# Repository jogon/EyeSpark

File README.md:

EyeSpark
========
EyeSpark brings to users a new and innovative way of interacting with computers. It allows users to control their mouse and keyboard with only their eyes and head. EyeSpark consists of a head mounted device and an application running on the users computer. The head mounted device tracks eye and head movements and sends the information to the user's PC via USB. The EyeSpark application captures this information and uses it to create the mapping of eye and head gestures to mouse and keystrokes. Users can fully customize the mappings and tie them to specific applications, allowing EyeSpark to work with a variety of applications.

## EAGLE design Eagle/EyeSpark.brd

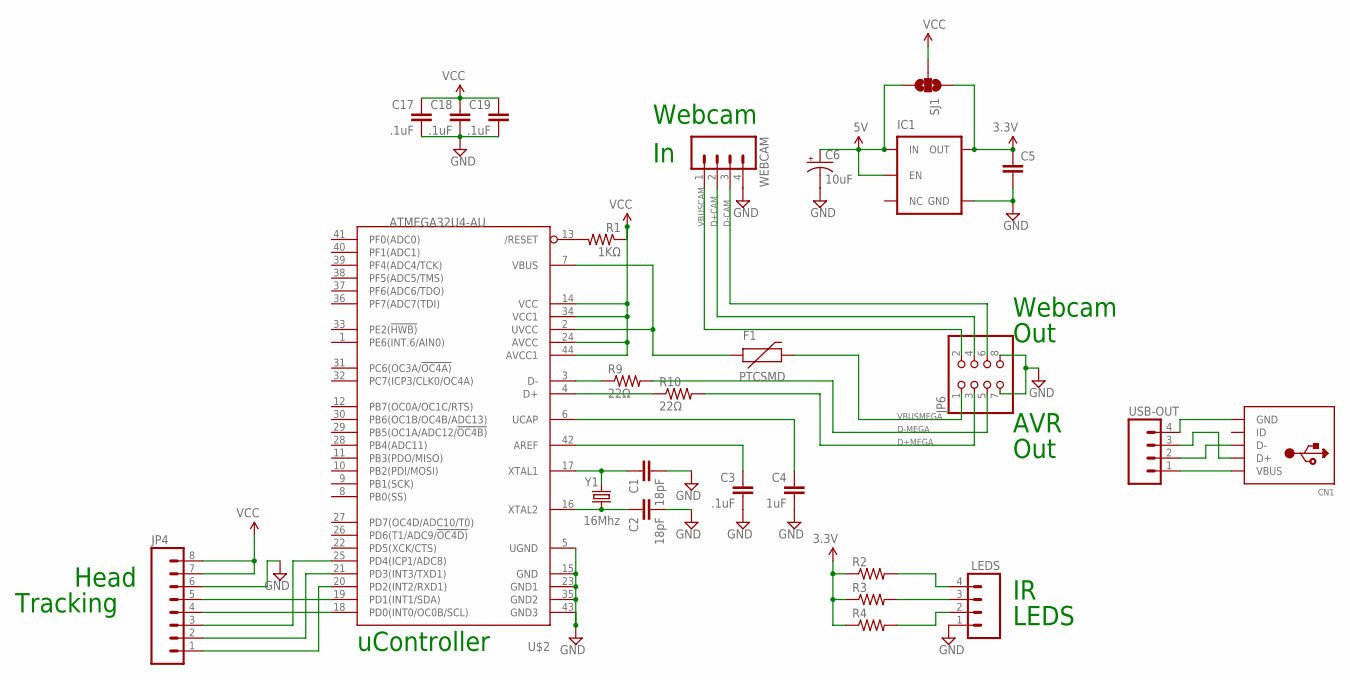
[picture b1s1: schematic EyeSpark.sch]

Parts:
C1, C2: 18pF; 0805
C3, C17, C18, C19: .1uF; 0805
C4: 1uF; 0805
C5: CAP0805; 0805
C6: 10uF; EIA7343
CN1: USBMINIB; USB-MINIB
F1: PTCSMD; PTC-1206
IC1: V_REG_TPS76433SOT23-5; SOT23-5
JP4: M08LOCK; 1X08_LOCK
JP6: PINHD-2X4; 2X04
LEDS: M04PTH; 1X04
R1: 1KΩ; 0805
R2, R3, R4: RESISTOR1206; 1206
R9, R10: 22Ω; 0805
SJ1: SOLDERJUMPER_2WAYT; SJ_2
U$2: ATMEGA32U4-AU; TQFP44
USB-OUT: M04PTH; 1X04
WEBCAM: M04LOCK_LONGPADS; 1X04_LOCK_LONGPADS
Y1: 16Mhz; CRYSTAL-SMD-5X3

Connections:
3.3V: C5.1, IC1.5 (OUT), R2.1, R3.1, R4.1, SJ1.1
5V: C6.A (+), IC1.1 (IN), IC1.3 (EN), SJ1.3
D+CAM: JP6.4, WEBCAM.2
D+MEGA: JP6.3, R10.2
D-CAM: JP6.6, WEBCAM.3
D-MEGA: JP6.5, R9.2
GND: C1.2, C2.2, C3.2, C4.2, C5.2, C6.C (-), C17.2, C18.2, C19.2, IC1.2 (GND), JP4.6, JP6.7, JP6.8, LEDS.1, U$2.5 (UGND), U$2.15 (GND), U$2.23 (GND1), U$2.35 (GND2), U$2.43 (GND3), WEBCAM.4
unnamed: C3.1, U$2.42 (AREF)
unnamed: C4.1, U$2.6 (UCAP)
unnamed: R1.2, U$2.13 (/RESET)
unnamed: R9.1, U$2.3 (D-)
unnamed: R10.1, U$2.4 (D+)
unnamed: JP4.4, U$2.18 (PD0(INT0/OC0B/SCL))
unnamed: C2.1, U$2.16 (XTAL2), Y1.3 (2)
unnamed: C1.1, U$2.17 (XTAL1), Y1.1
unnamed: JP4.1, U$2.20 (PD2(INT2/RXD1))
unnamed: LEDS.4, R2.2
unnamed: JP4.2, U$2.21 (PD3(INT3/TXD1))
unnamed: JP4.5, U$2.19 (PD1(INT1/SDA))
unnamed: JP4.3, U$2.25 (PD4(ICP1/ADC8))
unnamed: LEDS.3, R3.2
unnamed: F1.1, U$2.2 (UVCC), U$2.7 (VBUS)
unnamed: LEDS.2, R4.2
unnamed: CN1.VBUS, USB-OUT.1
unnamed: CN1.GND, USB-OUT.4
unnamed: CN1.D-, USB-OUT.2
unnamed: CN1.D+, USB-OUT.3
VBUSCAM: JP6.2, WEBCAM.1
VBUSMEGA: F1.2, JP6.1
VCC: C17.1, C18.1, C19.1, JP4.7, JP4.8, R1.1, SJ1.2, U$2.14 (VCC), U$2.24 (AVCC), U$2.34 (VCC1), U$2.44 (AVCC1)

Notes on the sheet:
uController
Webcam
Out
AVR
LEDS
Head
Tracking

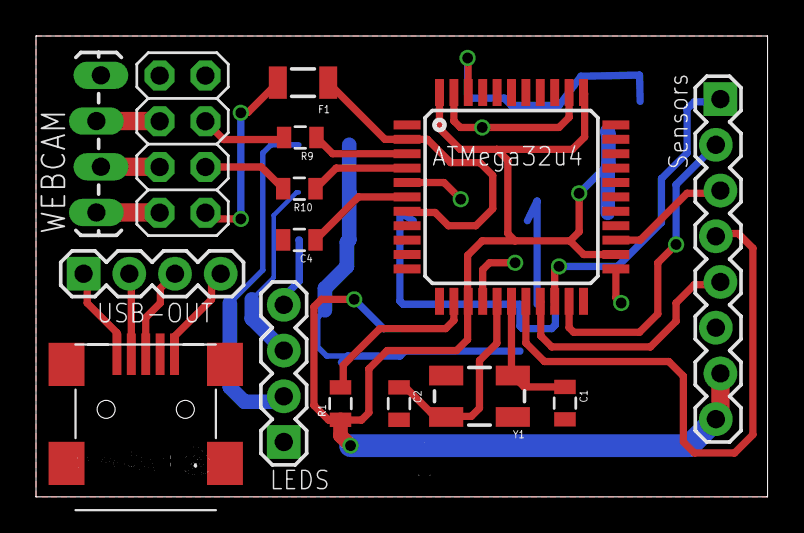
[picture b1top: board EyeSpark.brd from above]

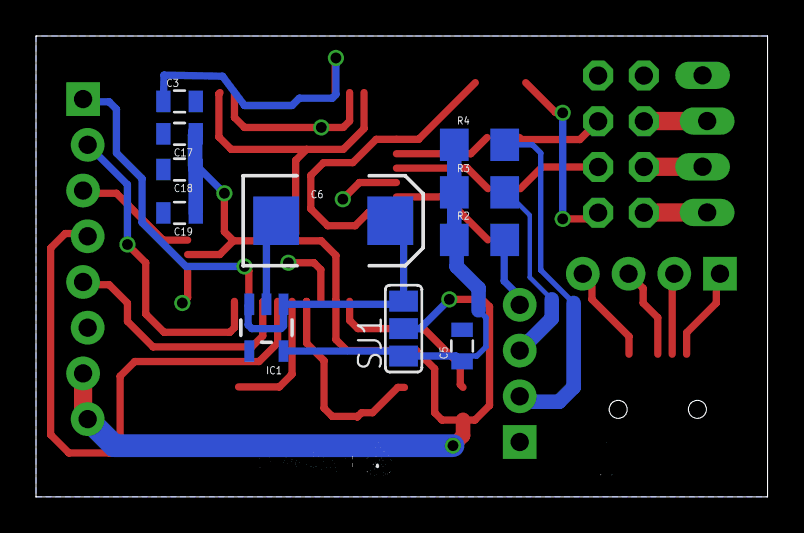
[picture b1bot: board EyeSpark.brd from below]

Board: 2 copper layers, 40.6 x 25.6 mm, 28 parts (12 on the bottom side), 30 nets.

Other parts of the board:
U$3, U$4: EYESPARK_LOGO

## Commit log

2012-09-29 Initial ITU Gaze Tracker
    Migrated from SVN
2012-09-29 Moving files around
    Trying to get it to run on Visual Studio 2010.
2012-09-29 Updated Source Code to Visual 2010
2012-09-29 Test for Visual Studio.
2012-09-29 Visual Studio first stable build
    First stable and runnable build on VS. Includes the debug.
2012-10-12 Testing my ability to do commits
2012-10-29 Updated UI and made space
    Added "Mappings" option.
2012-11-09 No idea.
2012-11-09 First commit for HID AVR code.
2012-11-09 Added HID PC code.
2012-11-09 HID PC Code fix. Still needs some work.
    Some path issues with USB HID library. Will fix in later.
2012-11-09 Added Eagle CAD files.
    Also contains the gerber files that were sent to the fab house.
2012-11-09 Headtracking Stuff
2012-11-09 Github Config Edit
2012-11-13 New logs.
    Fun.
2012-11-13 Modified something, dun know.
2012-11-17 Cleaned up HID PC Code
    Added comments and removed all of the extra debugging stuff. Ready for
    integration.
2012-11-20 Updated debug folder and what not.
2012-11-21 Fixed taskbar title and icon
2012-11-21 renamed icon file
2012-11-21 Added ability to minimize main window into tray
    The settings window doesn't go to tray if opened though. Not sure if
    this is an issue.
2012-11-21 Application can now only close from system tray
2012-11-21 Wired the mappings button to a window
2012-11-21 Crude implementation of key mapping UI
2012-11-23 Stub implementation of the mappings window code
2012-11-24 Close to final implementation of mapping window
    All that's left is to add code to persist the data.
2012-11-24 Mapping window code done (not live yet)
2012-11-24 The mappings window is now live
2012-11-25 Hooked up stub head traking event
2012-11-25 Hooked up ability to send keys
2012-11-25 Second version of mappings window
2012-11-25 Bug fixing in the mappings window
2012-11-25 Ability to clear sequences inthe mappings window
2012-11-25 Styled the mappings window
2012-11-25 Implementing (Fixing) glint and trying to figure out some wierd code that makes 0 sense.
2012-11-25 Fixed crashing after minimizing settings window
2012-11-25 Solving merge issues
2012-11-25 Hooked events in mapping window buttons
2012-11-26 Initial head tracking software integration
2012-11-26 Fixed logic error. Almost finished with usb code.
2012-11-26 Made the mappings window draggable
2012-11-26 Added ability to recognize more keys
2012-11-26 Fixed flags not clearing after clearing sequence
2012-11-26 Added installer
    It runs at log in too after installed.
2012-11-26 App now closes properly when closed from taskbar
2012-11-26 Fixed app crashing when closing windows from bar
2012-11-27 Modified no camera on startup pop up for EyeSpark
2012-11-27 Integration of head tracking code
    Still some things missing
2012-11-27 Missing file from last commit
2012-11-28 Added ability to control thresholds via app
2012-11-28 Complete Head Tracking firmware
2012-11-28 Letters needed to be lowercase in my hash
2012-11-28 Forced pitch down events to map to mouse clicks
2012-11-28 Updated position of kbdbutton in mapping window
2012-11-29 Reuploading Head Tracking Firmware
    For some reason after I initially commited the head tracking firmware,
    the files did not uploaded

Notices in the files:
parts and their libraries:
SparkFun: Licensing: CC v3.0 Share-Alike You are welcome to use this library for commercial purposes.
